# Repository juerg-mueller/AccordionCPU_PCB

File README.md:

# AccordionCPU_PCB

PCB ist mit KiCad gezeichnet worden. Zur Programmierung der Firmware (firmware.bin) braucht man folgende Tools:

https://www.espressif.com/en/support/download/other-tools

[AkkordeonCPU.pdf](https://github.com/user-attachments/files/20022553/AkkordeonCPU.pdf)

Alle zur Bestückung notwendigen Teile können bei Reichelt.de bestellt werden:

Kondenstor 100nF: KERKO 100N (0.03 €)

Widerstände 33kOhm: 1/4W 33k (0.11 €)

Widerstände 220Ohm: 1/4W 220 (0.11 €)

Widerstand 1kOhm: 1/4W 1K (0.11 €)

IC-Sockel DIL 14: GS 14P (0.27 €)

IC 74HC00: SN 74HC00 (0.46 €)

Display: DEBO OLED2 0.96 (6 €)

ESP32-S3-DevKitC: ESP32-S3-DevKitC-1-N8R8 (ca. 16 €) / auch bei mouser.de: 356-EP32S3DVKTC1N8R8

Wannenstecker 20-polig gewinkelt: WSL 20W (0.31 €)

Pfostenbuchse 20-polig: PFL 20 (0.30 €)

Flachbandkabel 20-polig: AWG 28-20G 3M (3.20 €)

Wannenstecker 6-polig: WSL 6G (0.17 €)

Pfostenbuchse 6-polig: PFL 6 (0.24 €)

Anschlussklemme: AKL 101-02 (0.25 €)

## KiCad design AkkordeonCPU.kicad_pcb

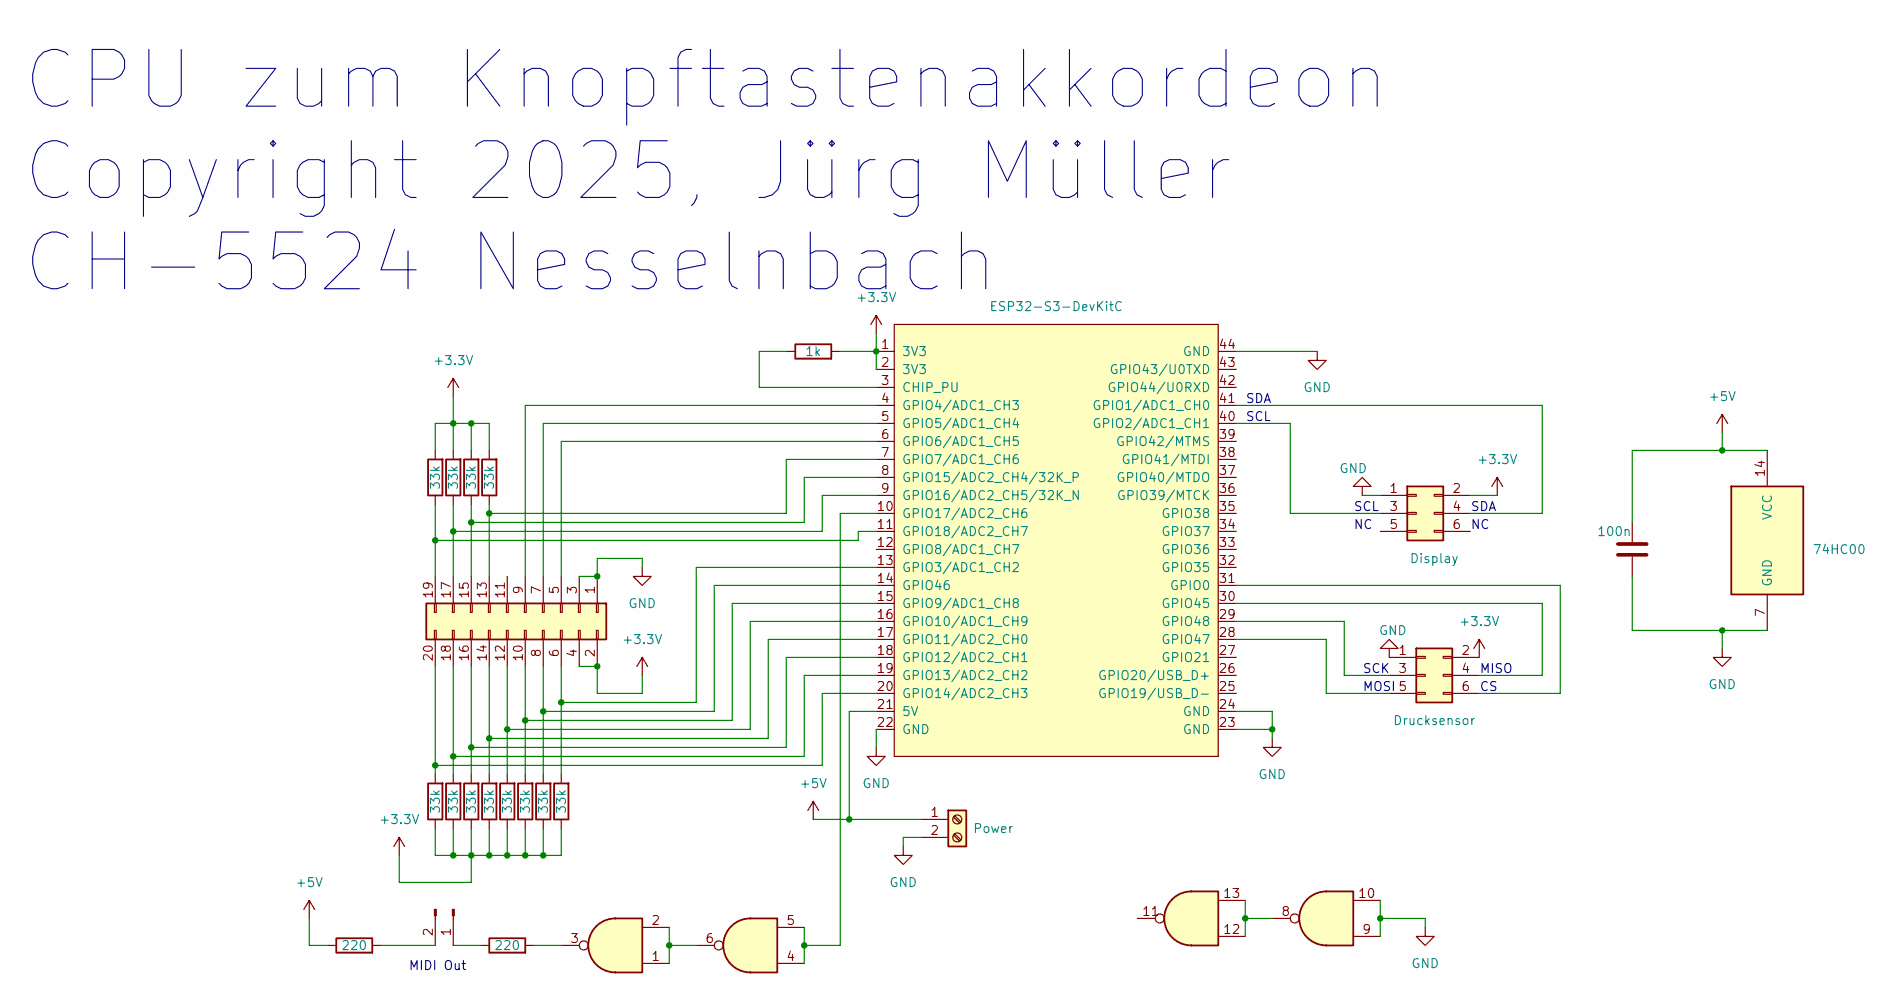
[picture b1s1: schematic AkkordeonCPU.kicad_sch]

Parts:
C1: 100n; C_Disc_D5.0mm_W2.5mm_P5.00mm
J1: MIDI Out; PinHeader_1x02_P2.54mm_Vertical
J2: Conn_02x10_Odd_Even; PinHeader_2x10_P2.54mm_Vertical
J3: Display; Box_2x3
J4: Drucksensor; Box_2x3
J8: Power; TerminalBlock_bornier-2_P5.08mm
R1, R15: 220; R_Axial_DIN0207_L6.3mm_D2.5mm_P10.16mm_Horizontal
R2, R3, R4, R5, R6, R7, R8, R9, R10, R11, R12, R13: 33k; R_Axial_DIN0207_L6.3mm_D2.5mm_P10.16mm_Horizontal
R14: 1k; R_Axial_DIN0207_L6.3mm_D2.5mm_P10.16mm_Horizontal
U1: 74HC00; DIP-14_W7.62mm_LongPads
U2: ESP32-S3-DevKitC

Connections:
+5V: C1.2, J8.1, R1.1, U1.14 (VCC), U2.21 (5V)
GND: C1.1, J2.1, J2.3, J3.1, J4.1, J8.2, U1.7 (GND), U1.9, U1.10, U2.22 (GND), U2.23 (GND), U2.24 (GND), U2.44 (GND)
unnamed: J1.1, R15.1
unnamed: J1.2, R1.2
unnamed: J2.5, U2.6 (GPIO6/ADC1_CH5)
unnamed: J2.6, R13.2, U2.13 (GPIO3/ADC1_CH2)
unnamed: J2.7, U2.5 (GPIO5/ADC1_CH4)
unnamed: J2.8, R12.2, U2.14 (GPIO46)
unnamed: J2.9, U2.4 (GPIO4/ADC1_CH3)
unnamed: J2.10, R11.2, U2.15 (GPIO9/ADC1_CH8)
unnamed: J2.12, R10.2, U2.16 (GPIO10/ADC1_CH9)
unnamed: J2.13, R8.1, U2.7 (GPIO7/ADC1_CH6)
unnamed: J2.14, R9.2, U2.17 (GPIO11/ADC2_CH0)
unnamed: J2.15, R6.1, U2.8 (GPIO15/ADC2_CH4/32K_P)
unnamed: J2.16, R7.2, U2.18 (GPIO12/ADC2_CH1)
unnamed: J2.17, R4.1, U2.9 (GPIO16/ADC2_CH5/32K_N)
unnamed: J2.18, R5.2, U2.19 (GPIO13/ADC2_CH2)
unnamed: J2.19, R2.1, U2.11 (GPIO18/ADC2_CH7)
unnamed: J2.20, R3.2, U2.20 (GPIO14/ADC2_CH3)
unnamed: J3.3, U2.40 (GPIO2/ADC1_CH1)
unnamed: J3.4, U2.41 (GPIO1/ADC1_CH0)
unnamed: J4.3, U2.29 (GPIO48)
unnamed: J4.4, U2.30 (GPIO45)
unnamed: J4.5, U2.28 (GPIO47)
unnamed: J4.6, U2.31 (GPIO0)
unnamed: R14.1, U2.3 (CHIP_PU)
unnamed: R15.2, U1.3
unnamed: U1.1, U1.2, U1.6
unnamed: U1.4, U1.5, U2.10 (GPIO17/ADC2_CH6)
unnamed: U1.8, U1.12, U1.13

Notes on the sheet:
SCK
MISO
MOSI
MIDI Out
SCL
CPU zum Knopftastenakkordeon Copyright 2025, Jürg Müller CH-5524 Nesselnbach
SDA
SDA

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
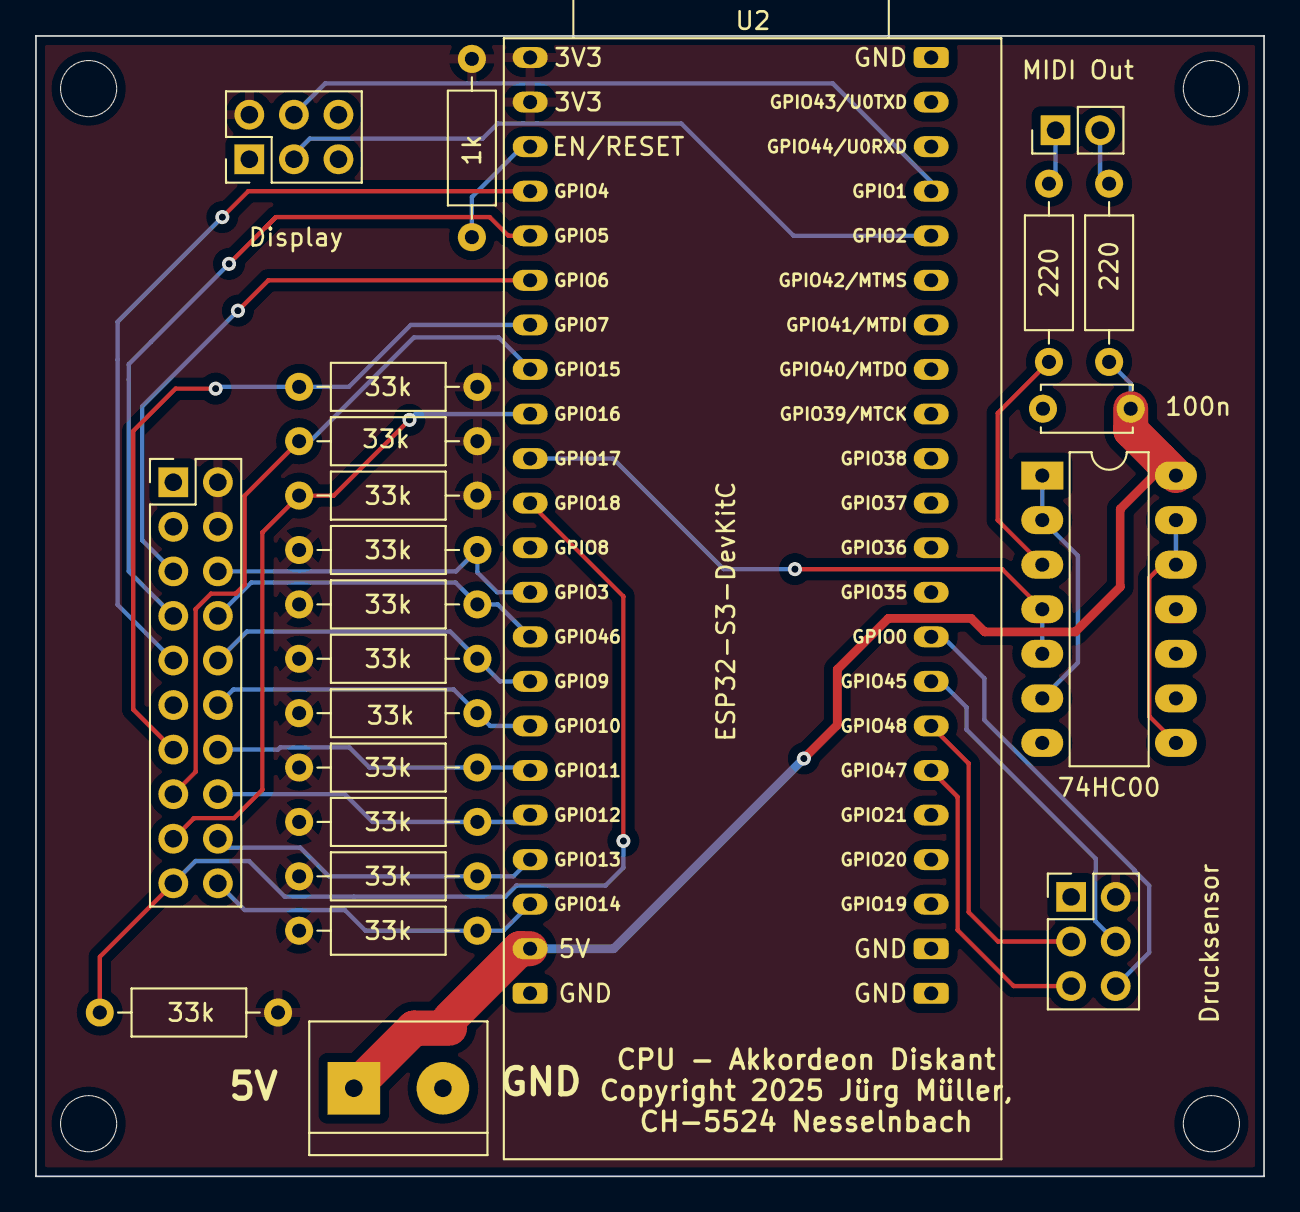
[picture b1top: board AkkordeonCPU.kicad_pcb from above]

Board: 2 copper layers, 70.0 x 65.0 mm, 27 parts (0 on the bottom side), 31 nets.

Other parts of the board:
REF2, REF2#2, REF2#3, REF2#4: MountingHole_3.2mm_M3_ISO7380
